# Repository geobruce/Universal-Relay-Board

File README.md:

# Universal-Relay-Board
This universal relay board is designed to be used. 
## Features:
- Extremely small footprint
- Comes in strips of 8 relays
- Break to desired size
- Power is common to all boards in row.
- 3.3V, 5V, 12V control signal compatible (3-20V)
- This board can be used with 3V - 24V relays (srd relay footprint Sanyou / Songle)
## Supplies
| What                  | Pieces | Aliexpress                                                                                                                                    | Ebay | Amazon |
| --------------------- | ------ | --------------------------------------------------------------------------------------------------------------------------------------------- | ---- | ------ |
| LL4148                | 1      | [100pcs ≃ €0.67](https://www.aliexpress.com/item/4000823542989.html) <br>  [500pcs ≃ €2.74](https://www.aliexpress.com/item/32825712013.html) |      |        |
| 2N7002                | 1      | [100pcs ≃ €1.82](https://www.aliexpress.com/item/2029421500.html)                                                                             |      |        |
| Screw terminal        | 1      | [100pcs ≃ €7.76](https://www.aliexpress.com/item/32658604595.html)                                                                            |      |        |
| Pin header            | 1      | [400pins ≃ €1.8](https://www.aliexpress.com/item/4000597872384.html)                                                                          |      |        |
| Relay 3V/5V/6V/9V/12V | 1      | [50pcs ≃ €15.24](https://www.aliexpress.com/item/32283519114.html)<br>[50pcs ≃ €25.23](https://www.aliexpress.com/item/4000386576222.html)    |
| 10k resistor          | 1      | [100pcs ≃ €0.54](https://www.aliexpress.com/item/32979436610.html)                                                                                          |

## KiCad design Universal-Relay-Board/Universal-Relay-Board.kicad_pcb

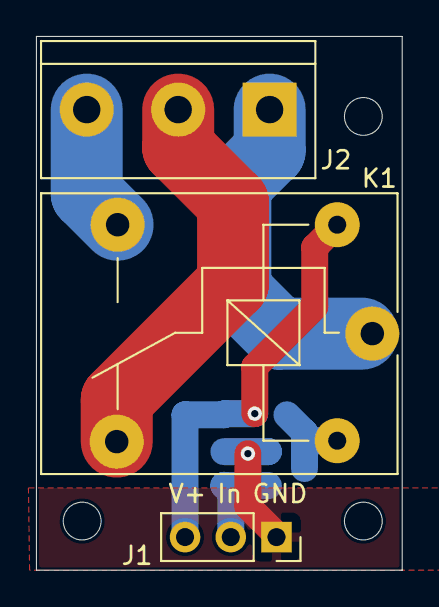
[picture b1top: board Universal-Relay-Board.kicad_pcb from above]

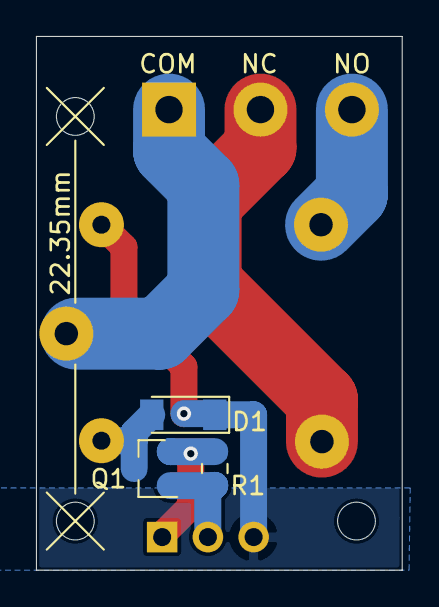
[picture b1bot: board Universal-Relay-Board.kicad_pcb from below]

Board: 2 copper layers, 20.3 x 29.7 mm, 9 parts (3 on the bottom side), 7 nets.

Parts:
D1: D_ALT; D_MiniMELF
H1, H2, H3: MountingHole; MountingHole_2.1mm
J1: Conn_01x03_Male; PinSocket_1x03_P2.54mm_Vertical
J2: Screw_Terminal_01x03; TerminalBlock_bornier-3_P5.08mm
K1: SRD-XXVDC-SL-C; Relay_SPDT_SANYOU_SRD_Series_Form_C
Q1: 2N7002; SOT-23
R1: 10K; R_0805_2012Metric

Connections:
/CH1/COM: J2.1, K1.1
/CH1/NC: J2.2, K1.4
/CH1/NO: J2.3, K1.3
/CH1/Relay_Magnet_B: D1.2, K1.5, Q1.3
GND: J1.1, Q1.2, R1.2
unnamed: J1.2, Q1.1, R1.1
VDD: D1.1, J1.3, K1.2

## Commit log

2020-04-08 blank kicad project
2020-04-08 Single channel schematic drawn
2020-04-08 single channel done
2020-04-09 multi channel done
2020-04-09 readme updated
